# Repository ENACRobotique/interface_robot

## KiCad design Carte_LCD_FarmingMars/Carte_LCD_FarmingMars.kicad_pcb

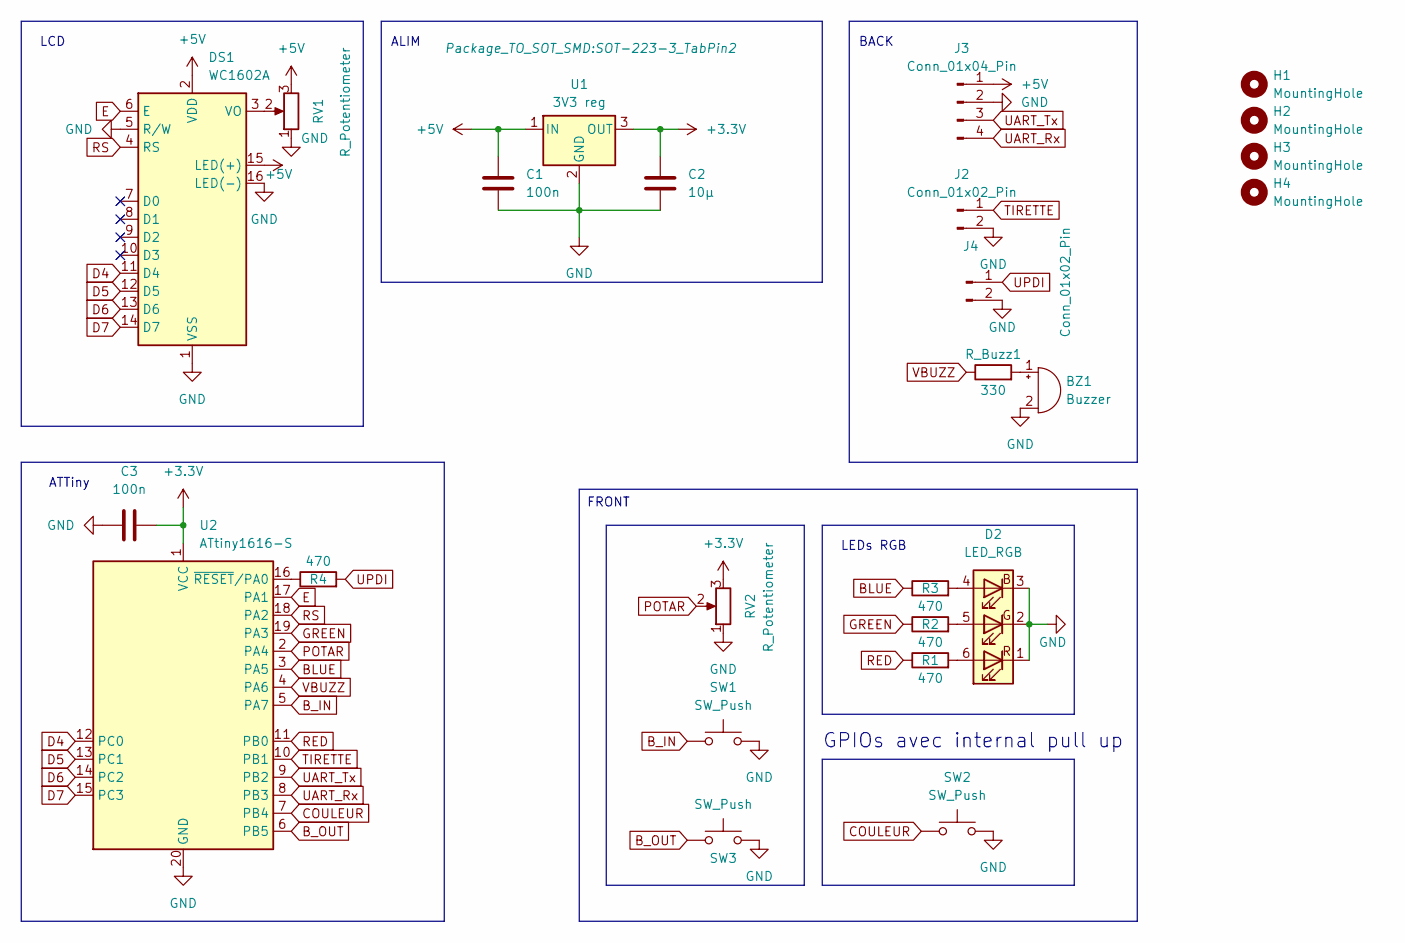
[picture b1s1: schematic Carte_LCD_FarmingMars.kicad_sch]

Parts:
BZ1: Buzzer; MagneticBuzzer_ProSignal_ABT-410-RC
C1, C3: 100n; C_0603_1608Metric
C2: 10µ; C_0603_1608Metric
D2: LED_RGB; PLCC6_CLP6C-FKB
DS1: WC1602A
H1, H2, H3, H4: MountingHole; MountingHole_3.2mm_M3
J2, J4: Conn_01x02_Pin; PinHeader_1x02_P2.54mm_Horizontal
J3: Conn_01x04_Pin; PinHeader_1x04_P2.54mm_Horizontal
R1, R2, R3, R4: 470; R_0603_1608Metric
RV1: R_Potentiometer; TS53YL
RV2: R_Potentiometer; Potentiometer_Bourns_PTV09A-1_Single_Vertical
R_Buzz1: 330; R_0603_1608Metric
SW1, SW2, SW3: SW_Push; SWITCH_DTSM31NV
U1: 3V3 reg; SOT-223-3_TabPin2
U2: ATtiny1616-S; SOIC-20W_7.5x12.8mm_P1.27mm

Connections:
+3.3V: C2.1, C3.2, RV2.3, U1.3 (OUT), U2.1 (VCC)
+5V: C1.1, DS1.2 (VDD), DS1.15 (LED(+)), J3.1, RV1.3, U1.1 (IN)
BLUE: R3.1, U2.3 (PA5)
B_IN: SW1.1, U2.5 (PA7)
B_OUT: SW3.1, U2.6 (PB5)
COULEUR: SW2.1, U2.7 (PB4)
D4: DS1.11 (D4), U2.12 (PC0)
D5: DS1.12 (D5), U2.13 (PC1)
D6: DS1.13 (D6), U2.14 (PC2)
D7: DS1.14 (D7), U2.15 (PC3)
E: DS1.6 (E), U2.17 (PA1)
GND: BZ1.2 (+), C1.2, C2.2, C3.1, D2.1 (RK), D2.2 (GK), D2.3 (BK), DS1.1 (VSS), DS1.5 (R/W), DS1.16 (LED(-)), J2.2, J3.2, J4.2, RV1.1, RV2.1, SW1.2, SW2.2, SW3.2, U1.2 (GND), U2.20 (GND)
GREEN: R2.1, U2.19 (PA3)
unnamed: BZ1.1 (-), R_Buzz1.2
unnamed: D2.4 (BA), R3.2
unnamed: D2.5 (GA), R2.2
unnamed: D2.6 (RA), R1.2
unnamed: DS1.3 (VO), RV1.2
unnamed: R4.1, U2.16 (~RESET/PA0)
POTAR: RV2.2, U2.2 (PA4)
RED: R1.1, U2.11 (PB0)
RS: DS1.4 (RS), U2.18 (PA2)
TIRETTE: J2.1, U2.10 (PB1)
UART_Rx: J3.4, U2.8 (PB3)
UART_Tx: J3.3, U2.9 (PB2)
UPDI: J4.1, R4.2
VBUZZ: R_Buzz1.1, U2.4 (PA6)

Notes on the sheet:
FRONT
LEDs RGB
GPIOs avec internal pull up
LCD
ATTiny
BACK
ALIM

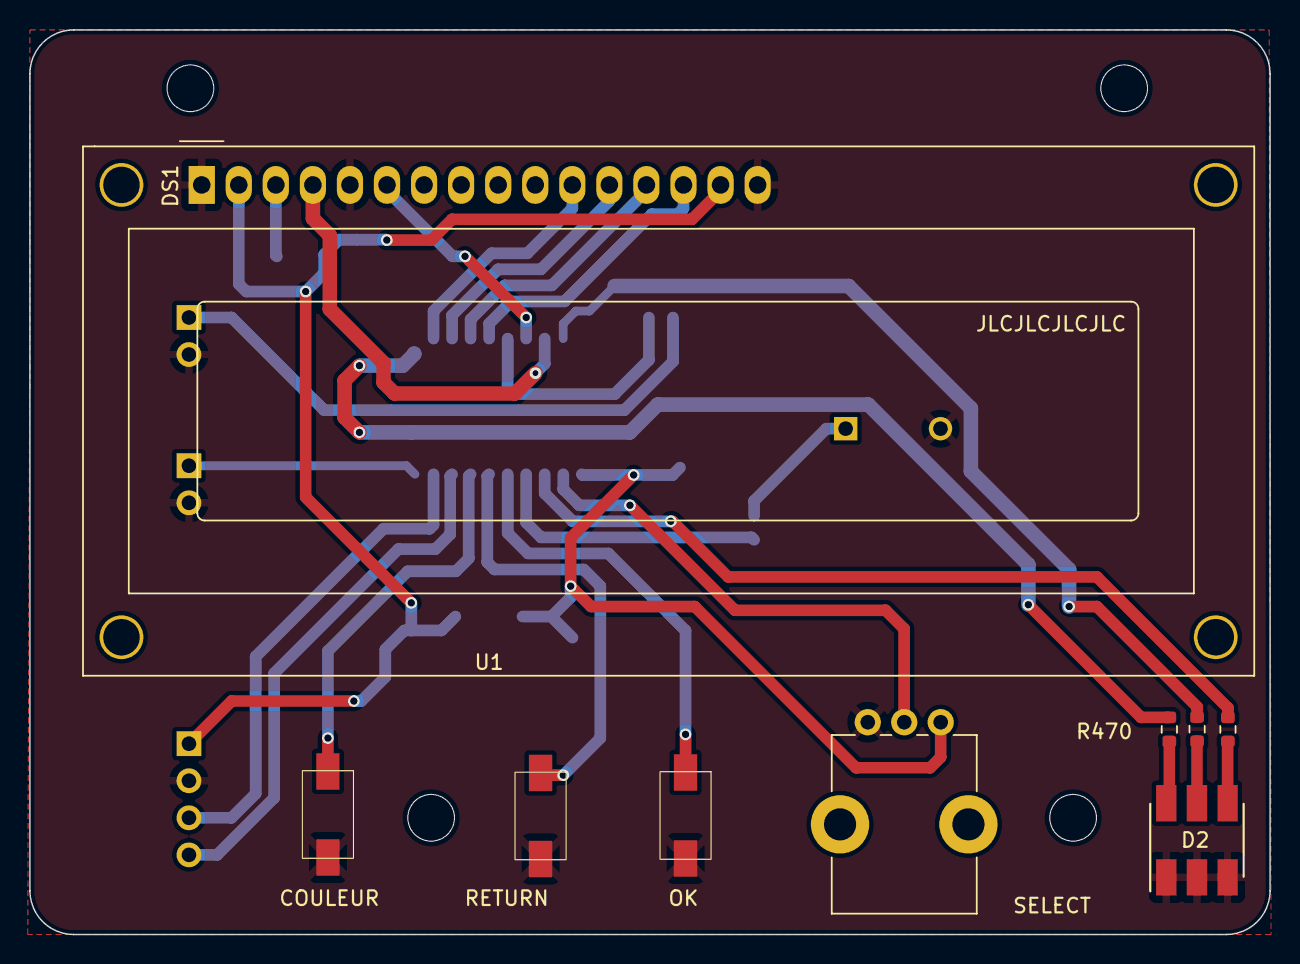
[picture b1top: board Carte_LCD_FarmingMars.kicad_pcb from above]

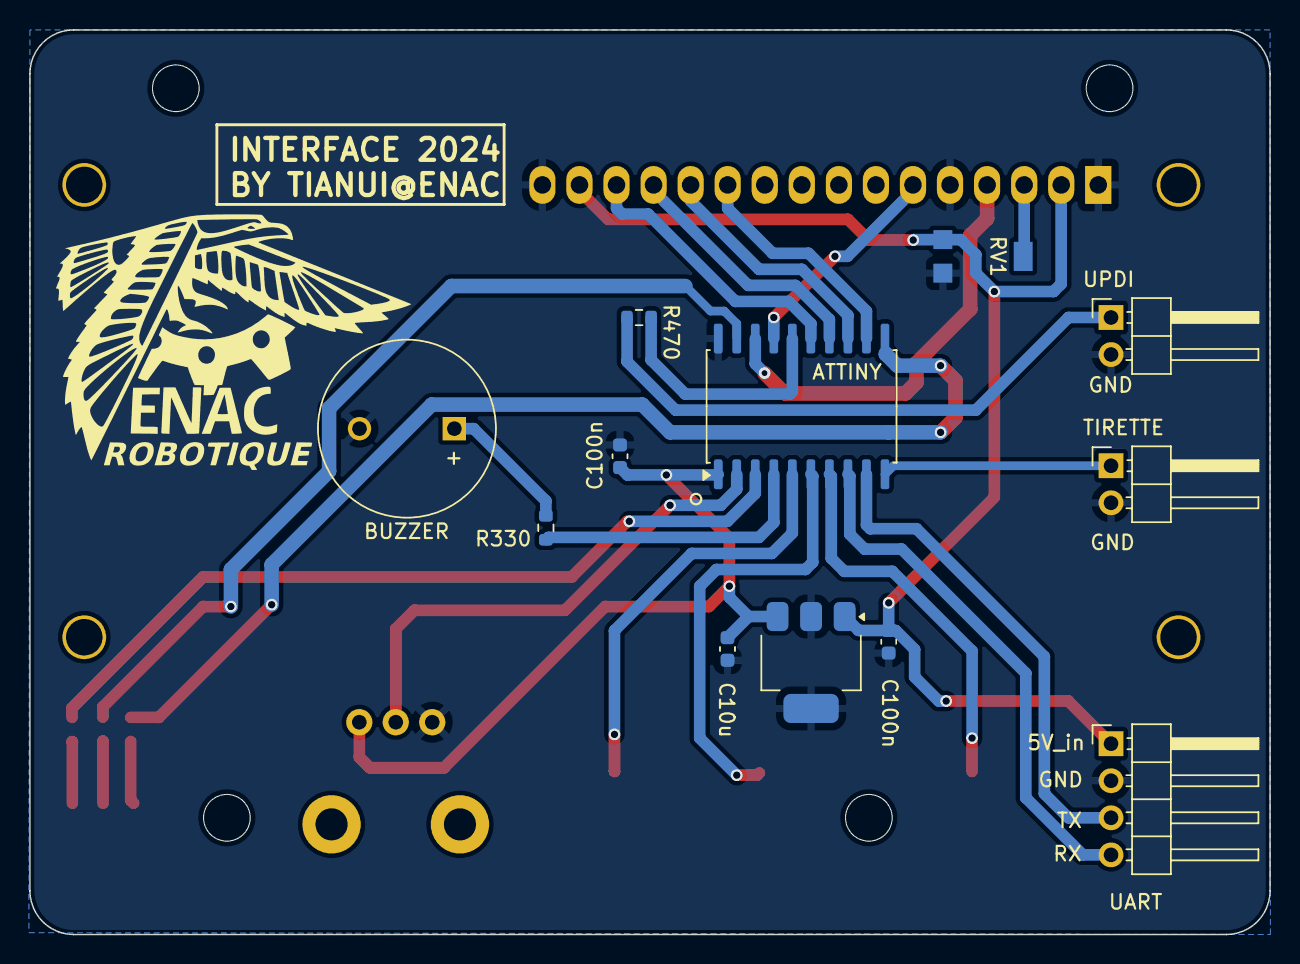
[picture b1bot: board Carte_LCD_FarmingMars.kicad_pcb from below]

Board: 2 copper layers, 85.0 x 62.0 mm, 25 parts (12 on the bottom side), 27 nets.

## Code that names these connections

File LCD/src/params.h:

#pragma once
#include <Arduino.h>

//////////////// pinout /////////////
constexpr pin_size_t LED_R = PIN_PA5;
constexpr pin_size_t LED_G = PIN_PA3;
constexpr pin_size_t LED_B = PIN_PB0;

constexpr pin_size_t BUZZ = PIN_PA6;

constexpr pin_size_t LCD_EN = PIN_PA1;
constexpr pin_size_t LCD_RS = PIN_PA2;
constexpr pin_size_t LCD_D4 = PIN_PC0;
constexpr pin_size_t LCD_D5 = PIN_PC1;
constexpr pin_size_t LCD_D6 = PIN_PC2;
constexpr pin_size_t LCD_D7 = PIN_PC3;

constexpr pin_size_t POTAR = PIN_PA4;
constexpr pin_size_t BTN_OK = PIN_PA7;
constexpr pin_size_t BTN_RET = PIN_PB5;
constexpr pin_size_t BTN_COLOR = PIN_PB4;
constexpr pin_size_t TIRETTE = PIN_PB1;

/////////////////////////////////////

constexpr int DEBOUNCE_VAL = 50;
constexpr uint32_t REPORT_PERIOD = 1000;
constexpr int POTAR_RESOLUTION = 5;

constexpr size_t REPORT_MSG_SIZE = 20;

// 16x2 characters + 3 leds + buzzer
constexpr size_t LCD_MSG_SIZE = 16*2 + 3 + 1;
constexpr size_t RCV_BUF_SIZE = LCD_MSG_SIZE + 1;   // lcd msg + \0

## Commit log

2024-01-25 Début LCD
2024-02-01 Followed discord changes
2024-02-01 Placement préliminaire PCB
2024-02-29 placement composants
2024-03-19 Routage, inversion pin Couleur et Vbuzz
2024-03-22 Corrections, Verification , prêt à commander !
2024-03-25 trou + bug footprints
2024-03-25 bug fixed : update footprints from library
2024-04-04 annotations
2024-04-08 ajoute texte et marque pin1
2024-04-08 remove fp-info-cache
2024-04-08 release V1
2024-04-17 code de test
2024-04-20 firmware LCD, à tester.
2024-04-20 Ajoute Open et Closed aux valeurs possible des boutons
2024-04-20 gère les erreurs de transmission
2024-04-20 Driver python
2024-04-22 fix firmaware and driver
